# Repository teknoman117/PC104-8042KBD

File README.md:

# PC104-8042KBD

An 8-bit PC/104 keyboard and mouse (PS2) controller for the Technologic Systems TS-3100 (https://www.embeddedarm.com/product-images/TS-3100), which lacks an integrated keyboard controller. Features a VT82C42N controller at the standard IO addresses and is wired to USB connectors. The USB connectors are wired to be equivalent to a passive USB to PS2 adapter, which requires compliant keyboards. Every standalone USB keyboard I've tried to date seemed to be compatible.

The keyboard interrupt is on IRQ 1 for a classic DOS PC, but this interrupt is not available on the PC/104 bus. The TS-3100 has a non-compliant PC/104 bus connector to begin with (most signals are LVCMOS33 due to usage of 74LVC parts and XC9500XL CPLDs, and the DMA pins are replaced with some board specific features like a 386EX chip select unit output and chip select signal overrides for the onboard flash memory), and has IRQ 1 wired in place of IOCHK on later revisions. A jumper is available to connect the keyboard interrupt to IOCHK, or a jumper wire can be used to connect it elsewhere. In the case of my TS-3100s, the IOCHK pin is not electrically connected anywhere, so I have a jumper wire to a GPIO header where IRQ 1 is broken out (DIO1 pin 14). A small BIOS hack is required to enable the IRQ 1 function on this pin at boot.

Licensed under CC-BY-SA 4.0

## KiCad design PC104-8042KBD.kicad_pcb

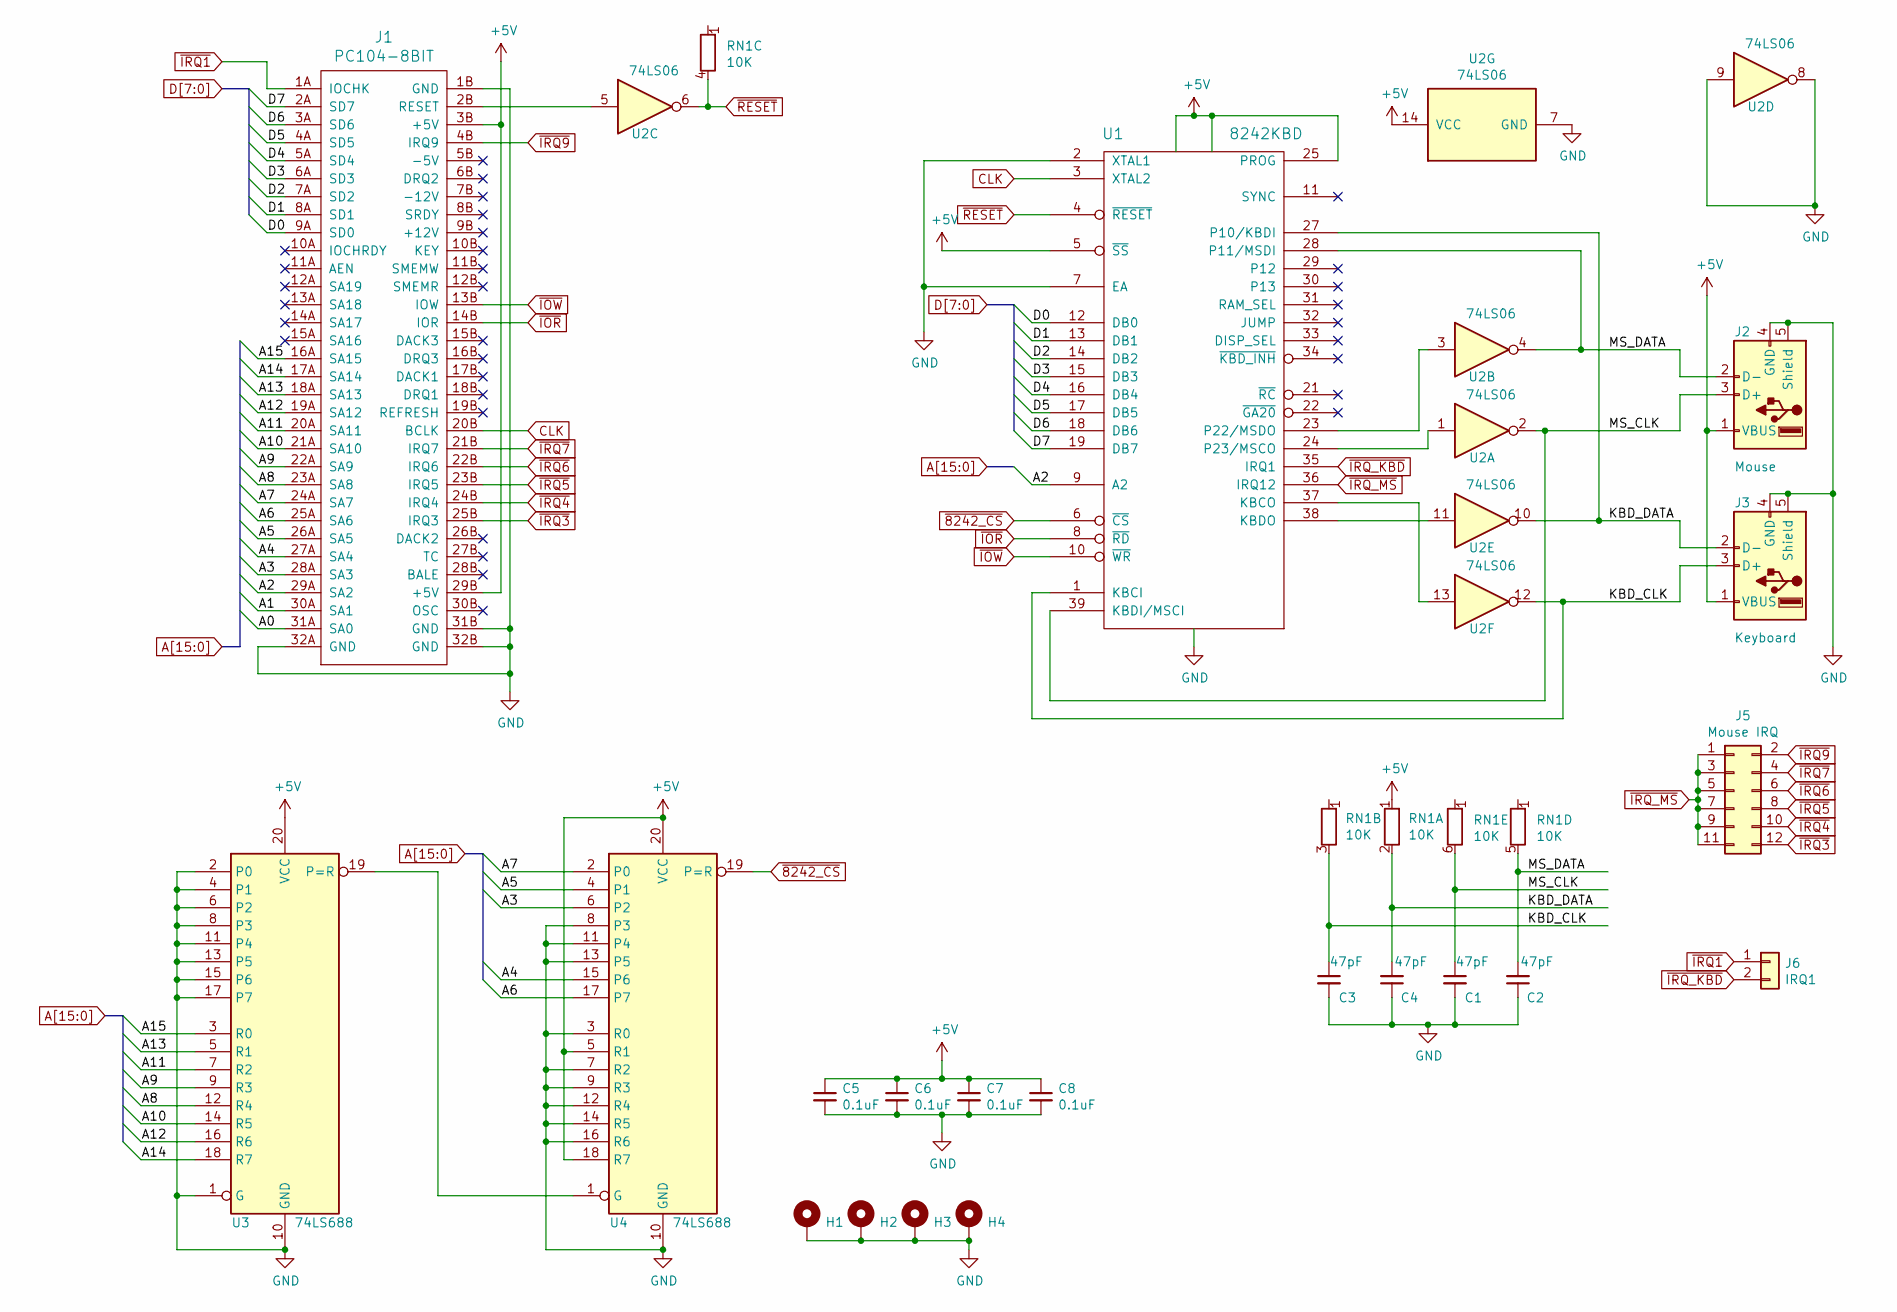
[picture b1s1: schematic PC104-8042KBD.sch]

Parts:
C1, C2, C3, C4: 47pF; C_Disc_D5.0mm_W2.5mm_P2.50mm
C5, C6, C7, C8: 0.1uF; C_Disc_D5.0mm_W2.5mm_P2.50mm
H1, H2, H3, H4: MountingHole_3.2mm_M3_Pad
J1: PC104-8BIT; PC104-8bit
J2: Mouse; USB_A_Molex_67643_Horizontal
J3: Keyboard; USB_A_Molex_67643_Horizontal
J5: Mouse IRQ; PinHeader_2x06_P2.54mm_Vertical
J6: IRQ1; PinHeader_1x02_P2.54mm_Horizontal
RN1: 10K; R_Array_SIP6
U1: 8242KBD; DIP-40_W15.24mm_Socket
U2: 74LS06; DIP-14_W7.62mm
U3, U4: 74LS688; DIP-20_W7.62mm_Socket

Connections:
+5V: C5.1, C6.1, C7.1, C8.1, J1.3B (+5V), J1.29B (+5V), J2.1 (VBUS), J3.1 (VBUS), RN1.1 (R1.1), U1.5 (~SS), U1.25 (PROG), U1.26 (VCC), U1.40 (VCC), U2.14 (VCC), U3.20 (VCC), U4.5 (R1), U4.18 (R7), U4.20 (VCC)
/A0: J1.31A (SA0)
/A1: J1.30A (SA1)
/A2: J1.29A (SA2), U1.9 (A2)
/A3: J1.28A (SA3), U4.6 (P2)
/A4: J1.27A (SA4), U4.15 (P6)
/A5: J1.26A (SA5), U4.4 (P1)
/A6: J1.25A (SA6), U4.17 (P7)
/A7: J1.24A (SA7), U4.2 (P0)
/A8: J1.23A (SA8), U3.12 (R4)
/A9: J1.22A (SA9), U3.9 (R3)
/A10: J1.21A (SA10), U3.14 (R5)
/A11: J1.20A (SA11), U3.7 (R2)
/A12: J1.19A (SA12), U3.16 (R6)
/A13: J1.18A (SA13), U3.5 (R1)
/A14: J1.17A (SA14), U3.18 (R7)
/A15: J1.16A (SA15), U3.3 (R0)
/D0: J1.9A (SD0), U1.12 (DB0)
/D1: J1.8A (SD1), U1.13 (DB1)
/D2: J1.7A (SD2), U1.14 (DB2)
/D3: J1.6A (SD3), U1.15 (DB3)
/D4: J1.5A (SD4), U1.16 (DB4)
/D5: J1.4A (SD5), U1.17 (DB5)
/D6: J1.3A (SD6), U1.18 (DB6)
/D7: J1.2A (SD7), U1.19 (DB7)
/KBD_CLK: C3.1, J3.3 (D+), RN1.3 (R2.2), U1.1 (KBCI), U2.12
/KBD_DATA: C4.2, J3.2 (D-), RN1.2 (R1.2), U1.27 (P10/KBDI), U2.10
/MS_CLK: C1.1, J2.3 (D+), RN1.6 (R5.2), U1.39 (KBDI/MSCI), U2.2
/MS_DATA: C2.2, J2.2 (D-), RN1.5 (R4.2), U1.28 (P11/MSDI), U2.4
CLK: J1.20B (BCLK), U1.3 (XTAL2)
GND: C1.2, C2.1, C3.2, C4.1, C5.2, C6.2, C7.2, C8.2, H1.1, H2.1, H3.1, H4.1, J1.1B (GND), J1.31B (GND), J1.32A (GND), J1.32B (GND), J2.4 (GND), J2.5 (Shield), J3.4 (GND), J3.5 (Shield), U1.2 (XTAL1), U1.7 (EA), U1.20 (GND), U2.7 (GND), U2.8, U2.9, U3.1 (G), U3.2 (P0), U3.4 (P1), U3.6 (P2), U3.8 (P3), U3.10 (GND), U3.11 (P4), U3.13 (P5), U3.15 (P6), U3.17 (P7), U4.3 (R0), U4.7 (R2), U4.8 (P3), U4.9 (R3), U4.10 (GND), U4.11 (P4), U4.12 (R4), U4.13 (P5), U4.14 (R5), U4.16 (R6)
unnamed: J1.2B (RESET), U2.5
unnamed: U1.23 (P22/MSDO), U2.3
unnamed: U1.24 (P23/MSCO), U2.1
unnamed: U1.37 (KBCO), U2.13
unnamed: U1.38 (KBDO), U2.11
unnamed: U3.19 (P=R), U4.1 (G)
~8242_CS: U1.6 (~CS), U4.19 (P=R)
~IOR: J1.14B (IOR), U1.8 (~RD)
~IOW: J1.13B (IOW), U1.10 (~WR)
~IRQ1: J1.1A (IOCHK), J6.1
~IRQ3: J1.25B (IRQ3), J5.12
~IRQ4: J1.24B (IRQ4), J5.10
~IRQ5: J1.23B (IRQ5), J5.8
~IRQ6: J1.22B (IRQ6), J5.6
~IRQ7: J1.21B (IRQ7), J5.4
~IRQ9: J1.4B (IRQ9), J5.2
~IRQ_KBD: J6.2, U1.35 (IRQ1)
~IRQ_MS: J5.1, J5.3, J5.5, J5.7, J5.9, J5.11, U1.36 (IRQ12)
~RESET: RN1.4 (R3.2), U1.4 (~RESET), U2.6

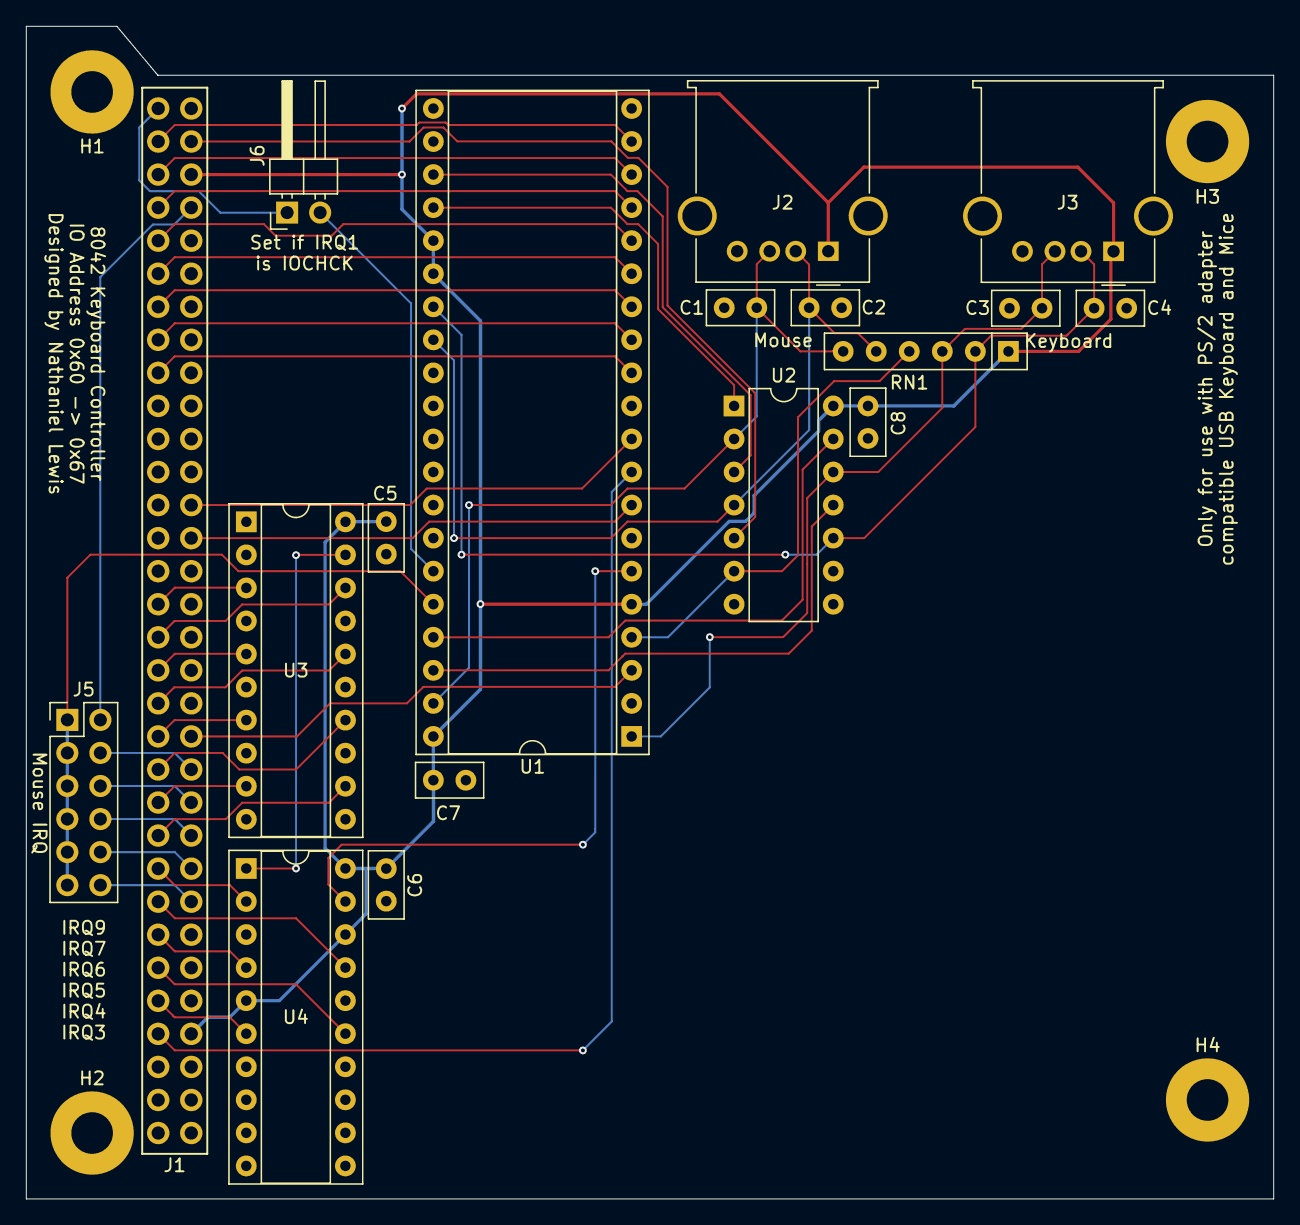
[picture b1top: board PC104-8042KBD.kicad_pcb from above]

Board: 2 copper layers, 95.9 x 90.1 mm, 22 parts (0 on the bottom side), 48 nets.

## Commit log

2021-04-15 state at manufacturing
2021-08-30 add a readme
2021-08-30 add photo of assembled board
2021-08-30 add gerbers for revision 1.0
2021-08-30 Licensed under CC-BY-SA 4.0
